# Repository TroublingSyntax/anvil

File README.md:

# anvil
STM32 based microcontroller personal project. Anvil is the first family of MCU's, focusing on simple pinouts and peripherals, only including connection peripherals and MCU hardware features. This repository is for tracking the physical design in KiCad. The board's firmware and other software is found elsewhere, mentioned in the README file.

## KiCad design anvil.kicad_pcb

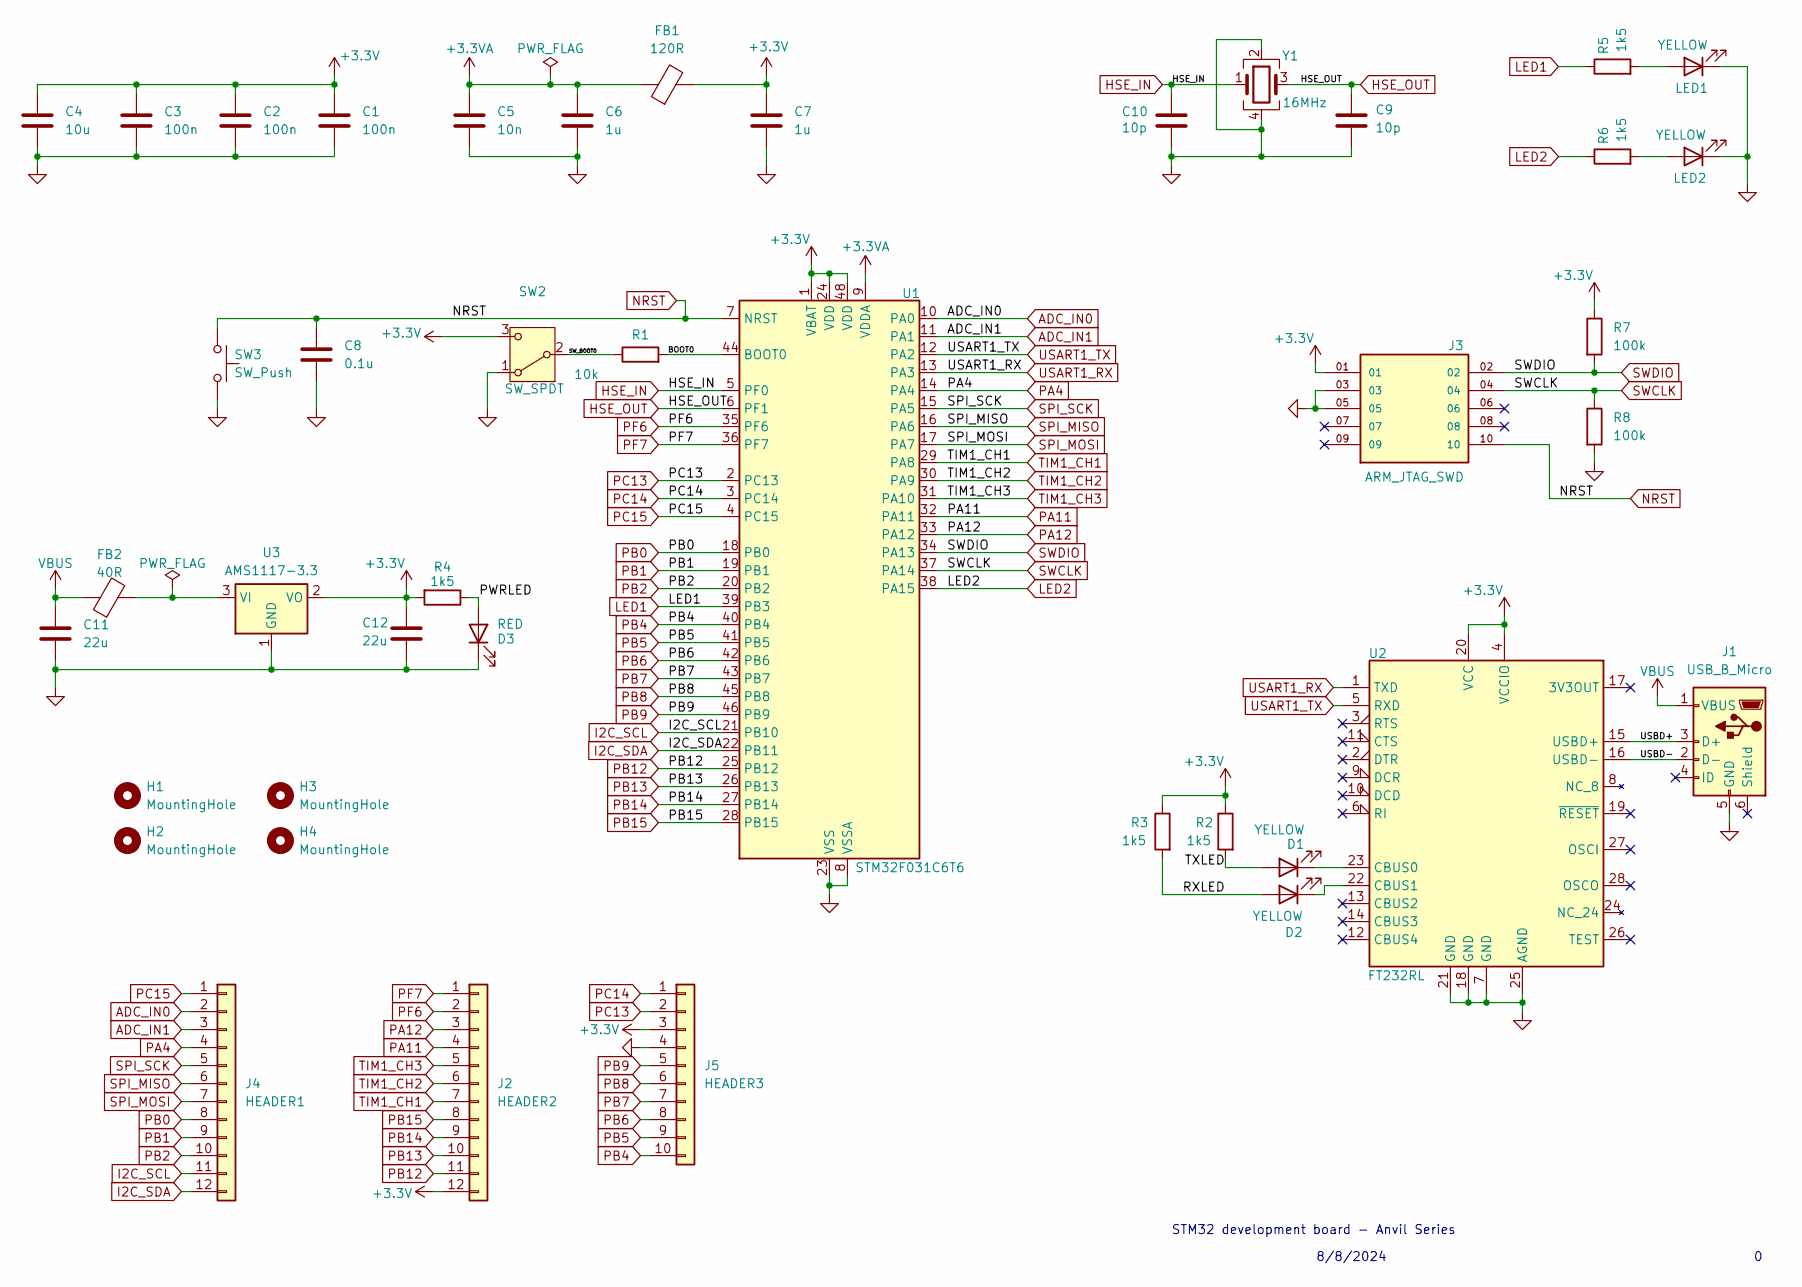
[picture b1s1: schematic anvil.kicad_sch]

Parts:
C1, C2, C3: 100n; C_0402_1005Metric
C4: 10u; C_0603_1608Metric
C5: 10n; C_0402_1005Metric
C6, C7: 1u; C_0402_1005Metric
C8: 0.1u; C_0402_1005Metric
C9, C10: 10p; C_0402_1005Metric
C11, C12: 22u; C_0805_2012Metric
D1, D2: YELLOW; LED_0603_1608Metric
D3: RED; LED_0603_1608Metric
FB1: 120R; L_0603_1608Metric
FB2: 40R; L_0603_1608Metric
H1, H2, H3, H4: MountingHole; MountingHole_2.2mm_M2
J1: USB_B_Micro; USB_Micro-B_Wuerth_629105150521
J2: HEADER2; PinSocket_1x12_P2.54mm_Vertical
J3: ARM_JTAG_SWD; FTSH-105-01-F-DV-P-TR; PARTREV R
J4: HEADER1; PinSocket_1x12_P2.54mm_Vertical
J5: HEADER3; PinSocket_1x10_P2.54mm_Vertical
LED1, LED2: YELLOW; LED_0603_1608Metric
R1: 10k; R_0402_1005Metric
R2, R3, R4, R5, R6: 1k5; R_0402_1005Metric
R7, R8: 100k; R_0603_1608Metric
SW2: SW_SPDT; SW_SPDT_PCM12
SW3: SW_Push; SW_PUSH_6mm
U1: STM32F031C6T6; LQFP-48_7x7mm_P0.5mm
U2: FT232RL; SSOP-28_5.3x10.2mm_P0.65mm
U3: AMS1117-3.3; SOT-223-3_TabPin2
Y1: 16MHz; Crystal_SMD_3225-4Pin_3.2x2.5mm

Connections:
+3.3V: C1.1, C2.1, C3.1, C4.1, C7.1, C12.1, FB1.2, J2.12, J3.01, J5.3, R2.1, R3.1, R4.2, R7.1, SW2.3 (C), U1.1 (VBAT), U1.24 (VDD), U1.48 (VDD), U2.4 (VCCIO), U2.20 (VCC), U3.2 (VO)
+3.3VA: C5.1, C6.1, FB1.1, U1.9 (VDDA)
/BOOT0: R1.2, U1.44 (BOOT0)
/PWRLED: D3.2 (A), R4.1
/RXLED: D2.2 (A), R3.2
/SW_BOOT0: R1.1, SW2.2 (B)
/TXLED: D1.2 (A), R2.2
/USBD+: J1.3 (D+), U2.15 (USBD+)
/USBD-: J1.2 (D-), U2.16 (USBD-)
ADC_IN0: J4.2, U1.10 (PA0)
ADC_IN1: J4.3, U1.11 (PA1)
GND: C1.2, C2.2, C3.2, C4.2, C5.2, C6.2, C7.2, C8.2, C9.2, C10.2, C11.2, C12.2, D3.1 (K), J1.5 (GND), J3.03, J3.05, J5.4, LED1.1 (K), LED2.1 (K), R8.2, SW2.1 (A), SW3.2, U1.8 (VSSA), U1.23 (VSS), U1.47 (VSS), U2.7 (GND), U2.18 (GND), U2.21 (GND), U2.25 (AGND), U3.1 (GND), Y1.2, Y1.4
HSE_IN: C10.1, U1.5 (PF0), Y1.1
HSE_OUT: C9.1, U1.6 (PF1), Y1.3
I2C_SCL: J4.11, U1.21 (PB10)
I2C_SDA: J4.12, U1.22 (PB11)
LED1: R5.1, U1.39 (PB3)
LED2: R6.1, U1.38 (PA15)
NRST: C8.1, J3.10, SW3.1, U1.7 (NRST)
unnamed: D1.1 (K), U2.23 (CBUS0)
unnamed: D2.1 (K), U2.22 (CBUS1)
unnamed: LED1.2 (A), R5.2
unnamed: LED2.2 (A), R6.2
unnamed: FB2.2, U3.3 (VI)
PA4: J4.4, U1.14 (PA4)
PA11: J2.4, U1.32 (PA11)
PA12: J2.3, U1.33 (PA12)
PB0: J4.8, U1.18 (PB0)
PB1: J4.9, U1.19 (PB1)
PB2: J4.10, U1.20 (PB2)
PB4: J5.10, U1.40 (PB4)
PB5: J5.9, U1.41 (PB5)
PB6: J5.8, U1.42 (PB6)
PB7: J5.7, U1.43 (PB7)
PB8: J5.6, U1.45 (PB8)
PB9: J5.5, U1.46 (PB9)
PB12: J2.11, U1.25 (PB12)
PB13: J2.10, U1.26 (PB13)
PB14: J2.9, U1.27 (PB14)
PB15: J2.8, U1.28 (PB15)
PC13: J5.2, U1.2 (PC13)
PC14: J5.1, U1.3 (PC14)
PC15: J4.1, U1.4 (PC15)
PF6: J2.2, U1.35 (PF6)
PF7: J2.1, U1.36 (PF7)
SPI_MISO: J4.6, U1.16 (PA6)
SPI_MOSI: J4.7, U1.17 (PA7)
SPI_SCK: J4.5, U1.15 (PA5)
SWCLK: J3.04, R8.1, U1.37 (PA14)
SWDIO: J3.02, R7.2, U1.34 (PA13)
TIM1_CH1: J2.7, U1.29 (PA8)
TIM1_CH2: J2.6, U1.30 (PA9)
TIM1_CH3: J2.5, U1.31 (PA10)
USART1_RX: U1.13 (PA3), U2.1 (TXD)
USART1_TX: U1.12 (PA2), U2.5 (RXD)
VBUS: C11.1, FB2.1, J1.1 (VBUS)

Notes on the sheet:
8/8/2024
STM32 development board - Anvil Series

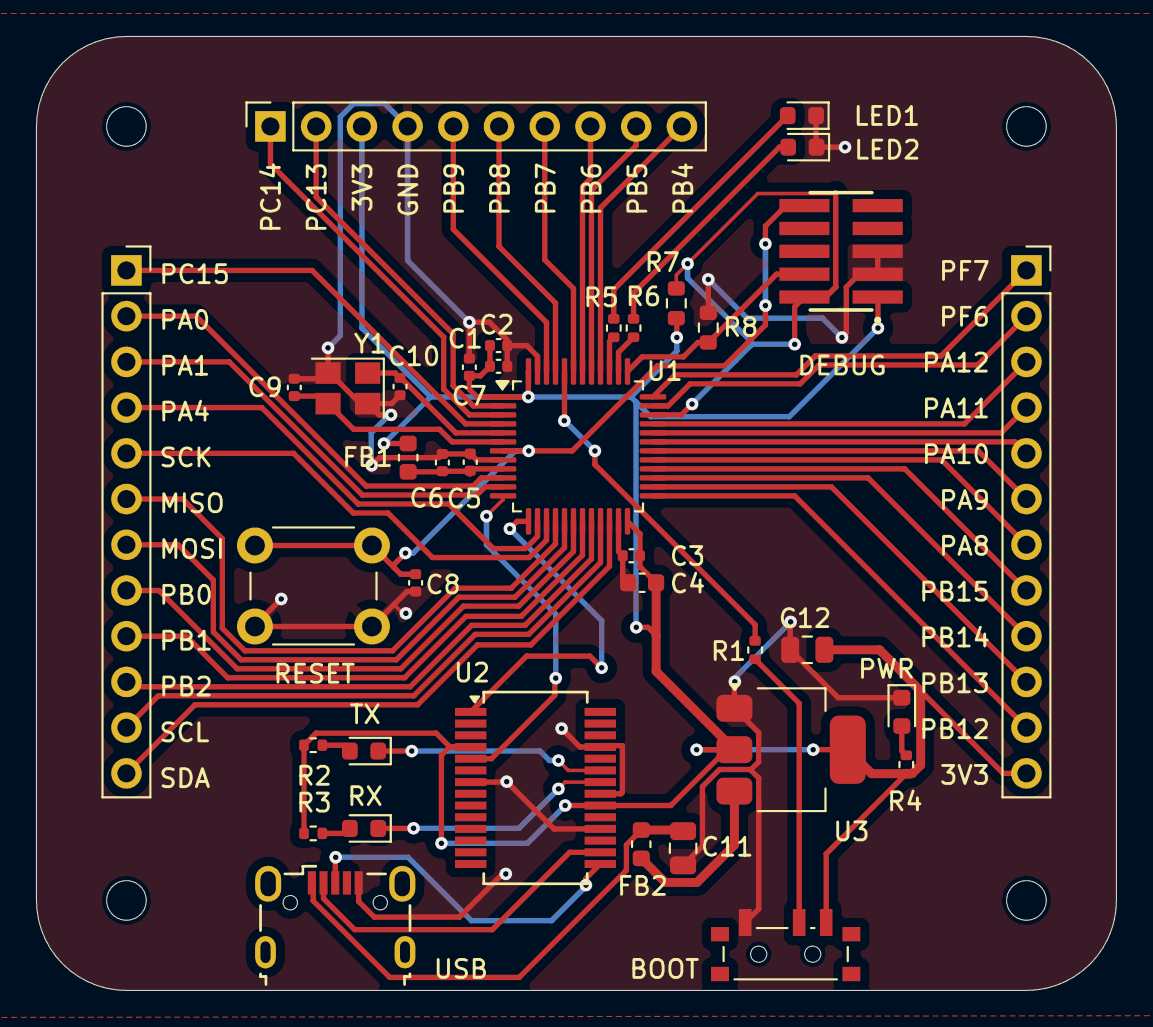
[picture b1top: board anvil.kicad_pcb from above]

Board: 2 copper layers, 60.0 x 53.0 mm, 42 parts (0 on the bottom side), 56 nets.

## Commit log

2025-03-18 anvil v1. Includes revision information.
